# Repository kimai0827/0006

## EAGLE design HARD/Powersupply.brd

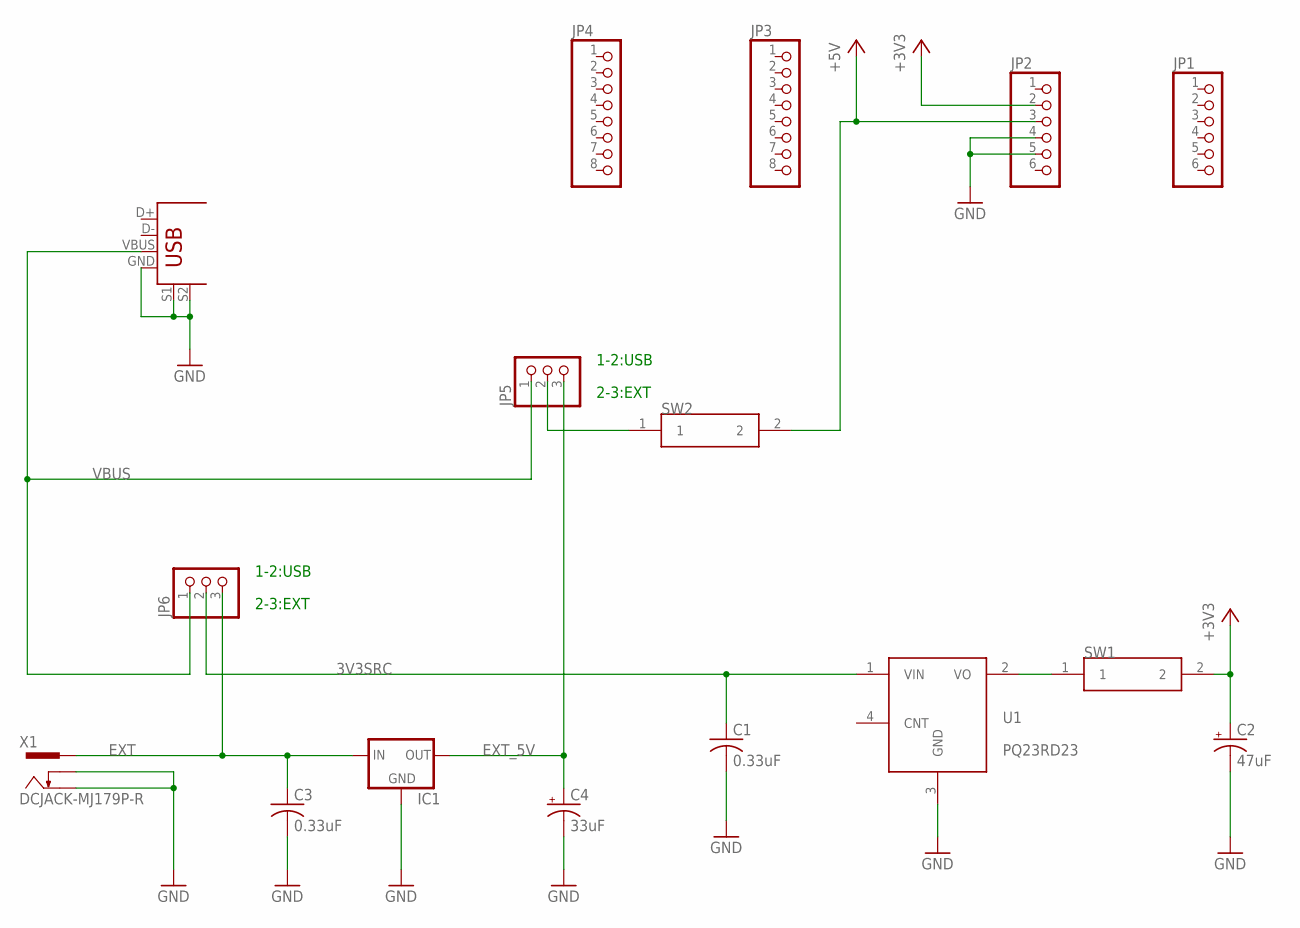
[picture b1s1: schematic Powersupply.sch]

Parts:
C1, C3: 0.33uF; C025-040X050
C2: 47uF; CPOL-US
C4: 33uF; CPOL-US
IC1: 78XXL
JP1, JP2: PINHD-1X6; 1X06
JP3, JP4: PINHD-1X8; 1X08
JP5, JP6: PINHD-1X3; 1X03
SW1, SW2: POLYSWITCH
U1: PQ23RD23; PQ3RD23
U$1: USB+SHIELD; USB-B-PTH
X1: DCJACK-MJ179P-R; MJ-179P-R

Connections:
3V3SRC: C1.1, JP6.2, U1.1 (VIN)
+3V3: C2.+, JP2.2, SW1.2
+5V: JP2.3, SW2.2
EXT: C3.1, IC1.IN, JP6.3, X1.1
EXT_5V: C4.+, IC1.OUT, JP5.3
GND: C1.2, C2.-, C3.2, C4.-, IC1.GND, JP2.4, JP2.5, U1.3 (GND), U$1.GND, U$1.S1, U$1.S2, X1.2, X1.3
unnamed: JP5.2, SW2.1
unnamed: SW1.1, U1.2 (VO)
VBUS: JP5.1, JP6.1, U$1.VBUS

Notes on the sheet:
1-2:USB
2-3:EXT

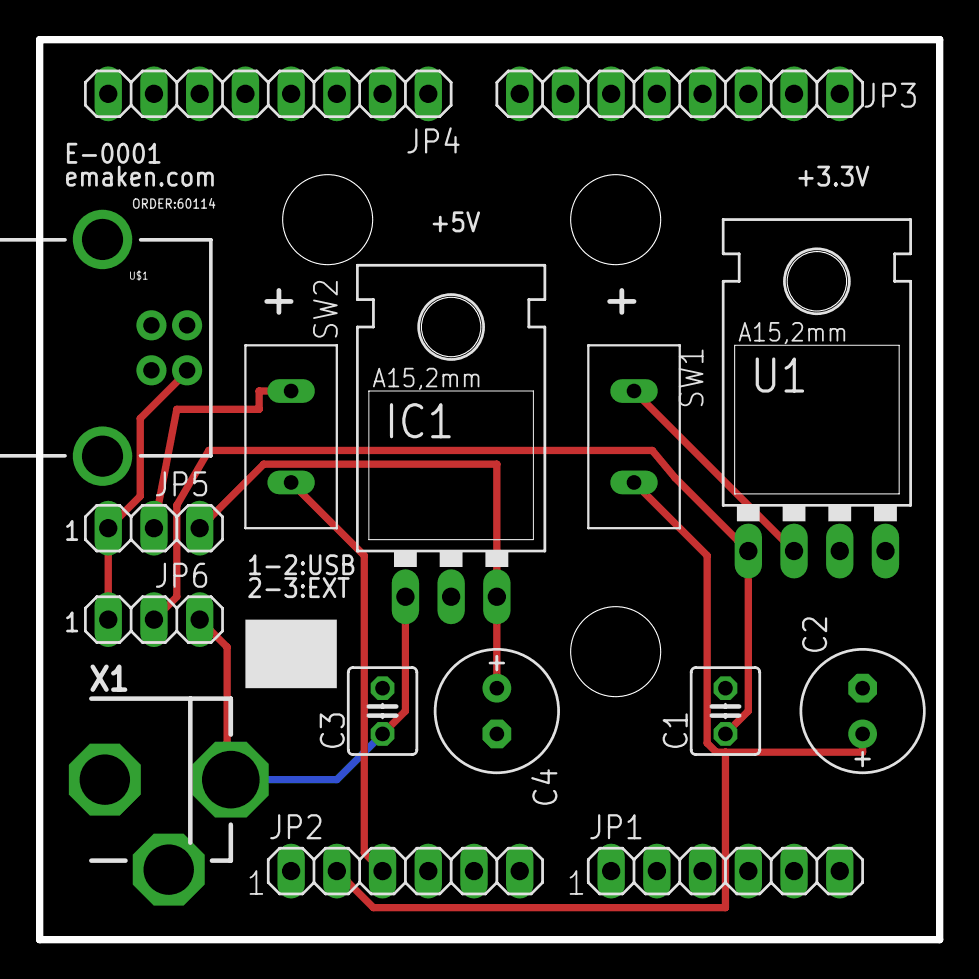
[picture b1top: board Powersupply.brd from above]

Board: 2 copper layers, 50.0 x 50.0 mm, 16 parts (0 on the bottom side), 9 nets.

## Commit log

2012-11-06 initial release

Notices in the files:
parts and their libraries:
SparkFun-Connectors: Licensing: CC v3.0 Share-Alike You are welcome to use this library for commercial purposes.
